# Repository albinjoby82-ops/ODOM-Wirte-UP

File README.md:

# ODOM POD Write-Up

The story of the ODOM POD: an ESP32-S3 odometry and localization pod that feeds pose to a VEX V5 brain over an RS-485 link.

This repo holds the narrative write-up. The operations team will turn it into a notebook, so each section is a self-contained, numbered document in `docs/`, meant to be read in order as one story.

## Reading order

| # | Section | Status |
|---|---------|--------|
| 1 | [Why These Components](docs/01-component-rationale.md) | Done |
| 2 | [What We Built on the Breadboard](docs/02-breadboard-firmware.md) | Done |
| 3 | [PCB V1](docs/03-pcb-v1.md) | Done |
| 4 | [PCB V2](docs/04-pcb-v2.md) | Done |

More sections will be added to this table as the story grows.

## What's in the repo

| Folder | What |
|---|---|
| [`docs/`](docs/) | The write-up, one numbered file per section, with images in `docs/img/` and clips in `docs/media/` |
| [`hardware/`](hardware/) | KiCad design files, Gerbers and PDFs for each PCB version |
| [`code/`](code/) | The pod firmware at each stage: breadboard, PCB V1 and PCB V2 |

## The story in one paragraph

The V5 brain is a good motor controller but a poor sensor platform. The ODOM POD moves sensing and pose estimation onto an ESP32-S3 and sends pose to the V5 as a pure sensor source. Motion control stays on the V5.

## Conventions

- One section per file in `docs/`, named `NN-short-title.md`, so the order is obvious and maps cleanly to notebook sections.
- Legality (VUR12) and latency points are woven into the relevant section, not split out.
- Figures and images go in `docs/img/` when they are added.

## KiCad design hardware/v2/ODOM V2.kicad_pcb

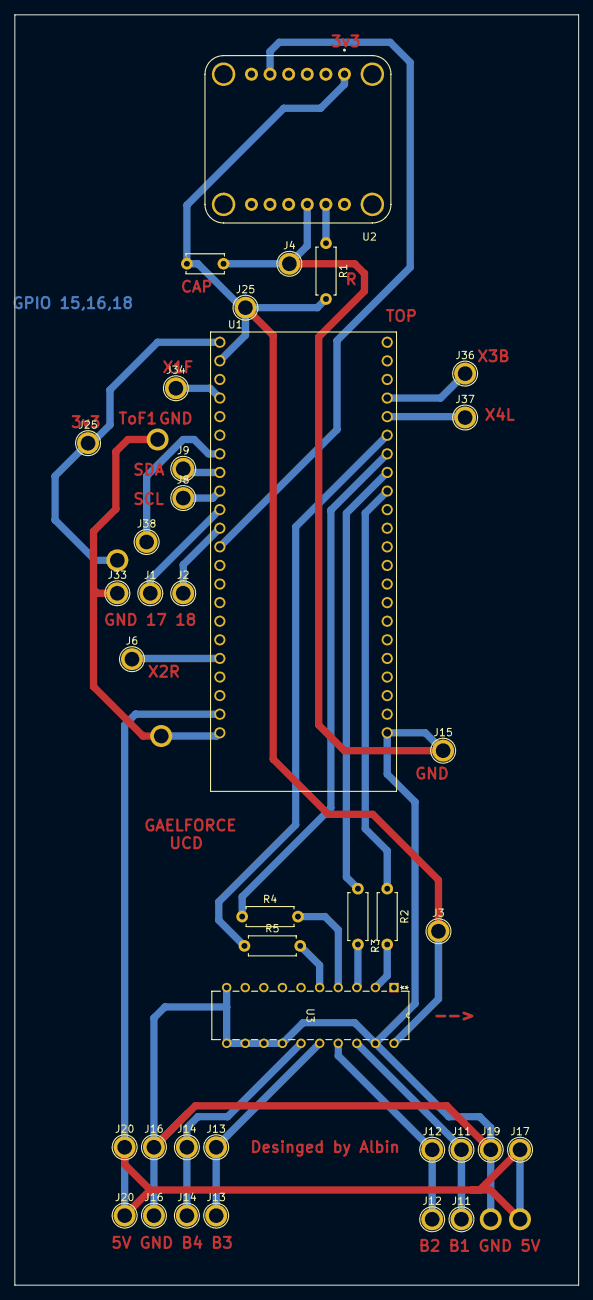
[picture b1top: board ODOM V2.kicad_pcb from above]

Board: 2 copper layers, 77.0 x 173.5 mm, 38 parts (0 on the bottom side), 26 nets.

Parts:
C1: C; C_Disc_D5.0mm_W2.5mm_P5.00mm
J1, J2, J3, J4, J6, J8, J9, J11, J11#2, J12, J12#2, J13, J13#2, J14, J14#2, J15, J16, J16#2, J17, J19, J20, J20#2, J25, J25#2, J33, J34, J36, J37, J38: Conn_01x01; TestPoint_Plated_Hole_D2.0mm
R1: 10K; R_Axial_DIN0207_L6.3mm_D2.5mm_P7.62mm_Horizontal
R2: 33; R_Axial_DIN0207_L6.3mm_D2.5mm_P7.62mm_Horizontal
R3, R4, R5: R; R_Axial_DIN0207_L6.3mm_D2.5mm_P7.62mm_Horizontal
U1: ESP32-S3-DEVKITC-1U-N8R8; MODULE_ESP32-S3-DEVKITC-1U-N8R8
U2: 4754; MODULE_4754
U3: SN74LVC245AN; N20

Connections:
+3V3: C1.2, J3.1 (Pin_1_1), J25.1 (Pin_1_1), J25#2.1 (Pin_1_1), R1.2, U1.J1_1 (3V3), U1.J1_2 (3V3__1), U2.JP1_1 (VIN), U3.20 (VCC)
+5V: J17.1 (Pin_1_1), J20.1 (Pin_1_1), J20#2.1 (Pin_1_1), U1.J1_21 (5V0)
/A1: R2.2, U3.2 (A1)
/A2: R3.2, U3.3 (A2)
/A3: R4.2, U3.4 (A3)
/A4: R5.2, U3.5 (A4)
/B1: J11.1 (Pin_1_1), J11#2.1 (Pin_1_1), U3.18 (B1)
/B2: J12.1 (Pin_1_1), J12#2.1 (Pin_1_1), U3.17 (B2)
/B3: J13.1 (Pin_1_1), J13#2.1 (Pin_1_1), U3.16 (B3)
/B4: J14.1 (Pin_1_1), J14#2.1 (Pin_1_1), U3.15 (B4)
/GP1: R2.1, U1.J3_9 (MTCK/GPIO39)
/GP2: R3.1, U1.J3_8 (MTDO/GPIO40)
/GP3: R4.1, U1.J3_7 (MTDI/GPIO41)
/GP4: R5.1, U1.J3_6 (MTMS/GPIO42)
/GP7: J38.1 (Pin_1_1), U1.J1_7 (GPIO7)
/GP12: J6.1 (Pin_1_1), U1.J1_18 (GPIO12)
/GP15: J9.1 (Pin_1_1), U1.J1_8 (GPIO15)
/GP16: J8.1 (Pin_1_1), U1.J1_9 (GPIO16)
/GP17: J1.1 (Pin_1_1), U1.J1_10 (GPIO17)
/GP18: J2.1 (Pin_1_1), U1.J1_11 (GPIO18)
/P0: R1.1, U2.JP2_2 (P0)
/SDA: U1.J1_12 (GPIO8), U2.JP1_5 (SDA)
/X1: J34.1 (Pin_1_1), U1.J1_4 (GPIO4)
/X3: J36.1 (Pin_1_1), U1.J3_4 (GPIO1)
/X4: J37.1 (Pin_1_1), U1.J3_5 (GPIO2)
GND: C1.1, J4.1 (Pin_1_1), J15.1 (Pin_1_1), J16.1 (Pin_1_1), J16#2.1 (Pin_1_1), J19.1 (Pin_1_1), J33.1 (Pin_1_1), U1.J1_22 (GND), U1.J3_22 (GND__3), U2.JP2_3 (P1), U3.10 (GND), U3.11 (B8), U3.12 (B7), U3.13 (B6), U3.14 (B5), U3.19 (*OE)
